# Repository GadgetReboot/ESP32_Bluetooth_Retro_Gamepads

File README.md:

# ESP32_Bluetooth_Retro_Gamepads
Use ESP32 to adapt modern bluetooth game controllers to retro console gamepads<BR><BR>
These PCBs are designed to plug into an ESP32 dev board but can work with 5V power and SPI signals<BR>
https://github.com/GadgetReboot/ESP32_5V_Dev_Board  <BR><BR>
The sketch is set up to auto detect which PCB is plugged in and send out the appropriate gamepad controls
based on PS4 controller activity.<br><br>
Video:<br><br>

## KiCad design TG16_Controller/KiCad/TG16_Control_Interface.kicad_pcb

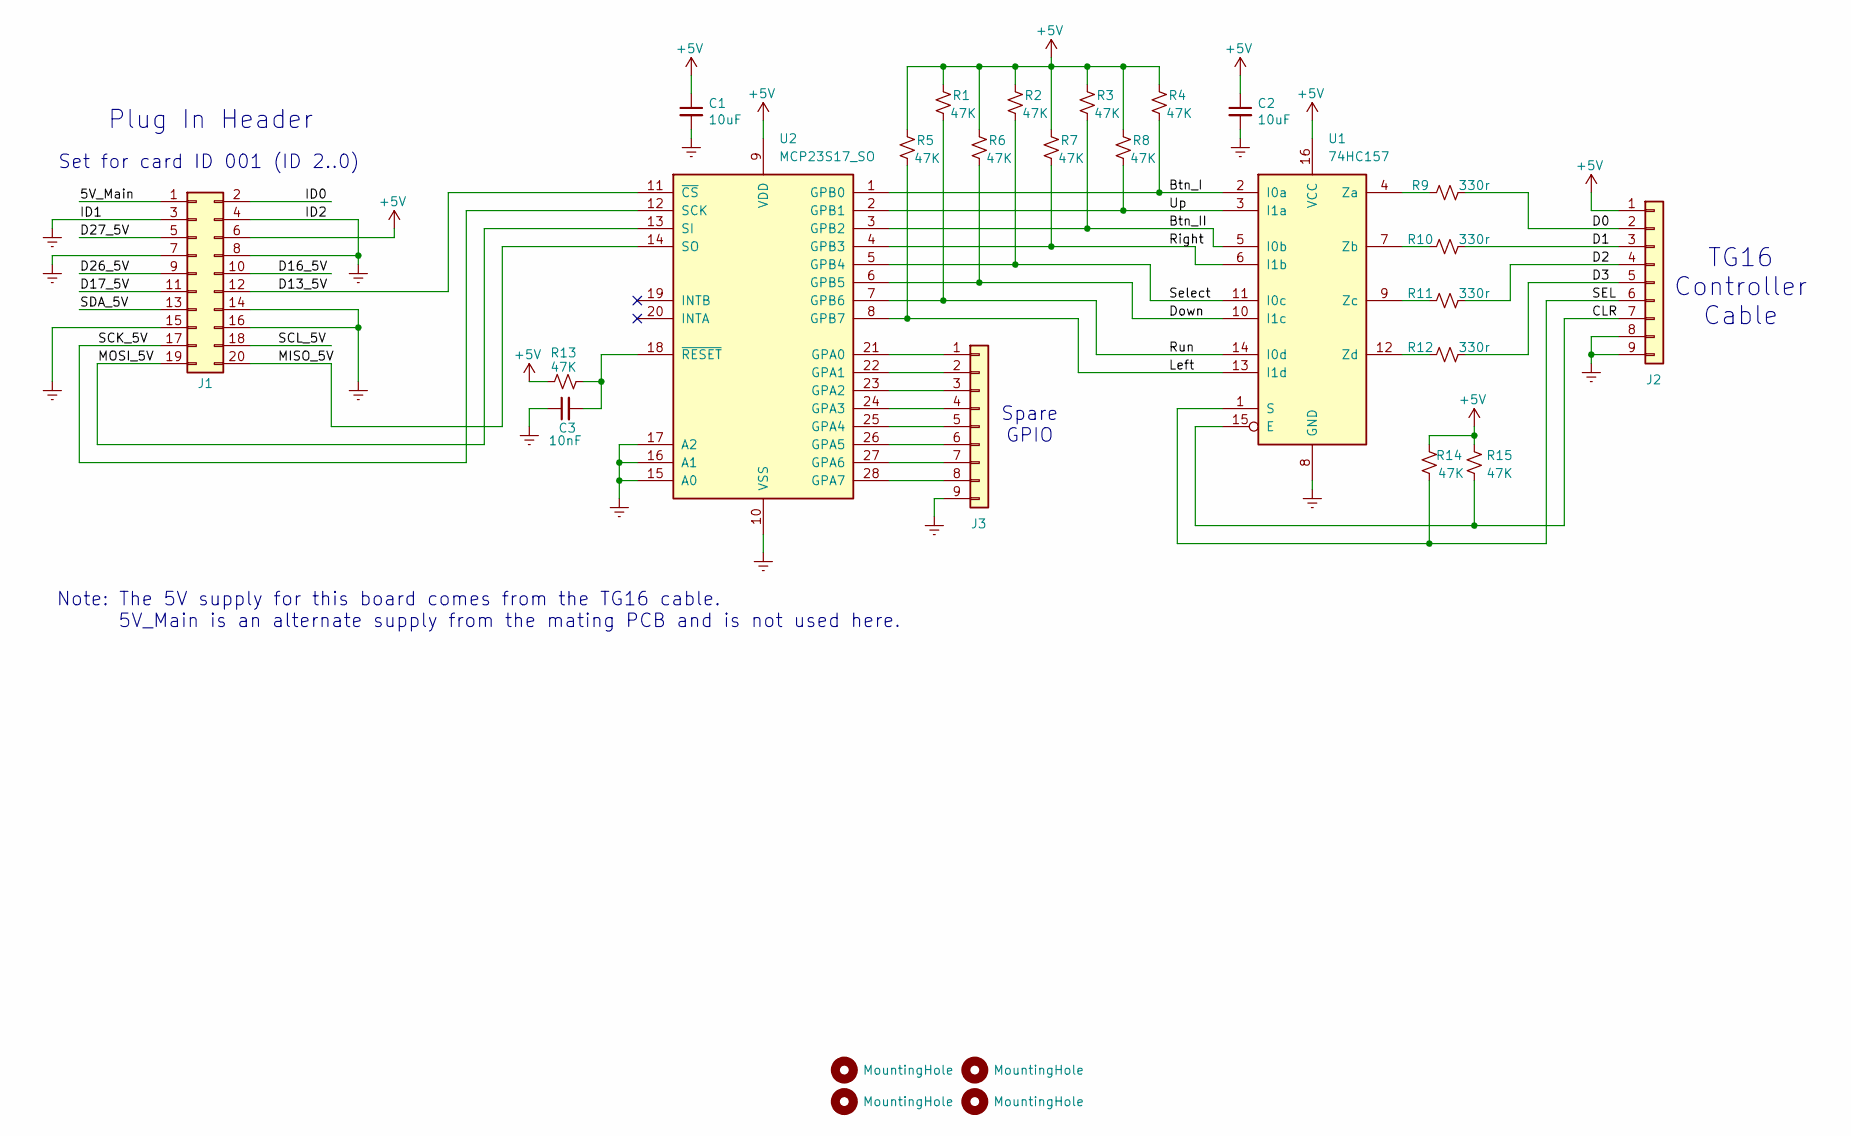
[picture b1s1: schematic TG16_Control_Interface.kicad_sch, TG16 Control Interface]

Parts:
C1, C2: 10uF; C_0805_2012Metric_Pad1.18x1.45mm_HandSolder
C3: 10nF; C_0805_2012Metric_Pad1.18x1.45mm_HandSolder
H1, H2, H3, H4: MountingHole; MountingHole_3.5mm
J1: Conn_02x10_Odd_Even; PinHeader_2x10_P2.54mm_Horizontal
J2: Conn_01x09; JST_XH_S9B-XH-A_1x09_P2.50mm_Horizontal
J3: Conn_01x09; PinHeader_1x09_P2.54mm_Vertical
R1, R2, R3, R4, R5, R6, R7, R8, R13, R14, R15: 47K; R_0805_2012Metric_Pad1.20x1.40mm_HandSolder
R9, R10, R11, R12: 330r; R_0805_2012Metric_Pad1.20x1.40mm_HandSolder
U1: 74HC157; SO-16_3.9x9.9mm_P1.27mm
U2: MCP23S17_SO; SOIC-28W_7.5x17.9mm_P1.27mm

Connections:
+5V: C1.1, C2.1, J1.6, J2.1, R1.1, R2.1, R3.1, R4.1, R5.1, R6.1, R7.1, R8.1, R13.1, R14.1, R15.1, U1.16 (VCC), U2.9 (VDD)
/5V_Main: J1.1
/Btn_I: R4.2, U1.2 (I0a), U2.1 (GPB0)
/Btn_II: R3.2, U1.5 (I0b), U2.3 (GPB2)
/CLR: J2.7, R15.2, U1.15 (E)
/D0: J2.2, R9.2
/D1: J2.3, R10.2
/D2: J2.4, R11.2
/D3: J2.5, R12.2
/D13_5V: J1.12, U2.11 (~CS)
/D16_5V: J1.10
/D17_5V: J1.11
/D26_5V: J1.9
/D27_5V: J1.5
/Down: R6.2, U1.10 (I1c), U2.6 (GPB5)
/ID0: J1.2
/Left: R5.2, U1.13 (I1d), U2.8 (GPB7)
/MISO_5V: J1.20, U2.14 (SO)
/MOSI_5V: J1.19, U2.13 (SI)
/Right: R7.2, U1.6 (I1b), U2.4 (GPB3)
/Run: R1.2, U1.14 (I0d), U2.7 (GPB6)
/SCK_5V: J1.17, U2.12 (SCK)
/SCL_5V: J1.18
/SDA_5V: J1.13
/SEL: J2.6, R14.2, U1.1 (S)
/Select: R2.2, U1.11 (I0c), U2.5 (GPB4)
/Up: R8.2, U1.3 (I1a), U2.2 (GPB1)
GNDREF: C1.2, C2.2, C3.1, J1.3, J1.4, J1.7, J1.8, J1.14, J1.15, J1.16, J2.8, J2.9, J3.9, U1.8 (GND), U2.10 (VSS), U2.15 (A0), U2.16 (A1), U2.17 (A2)
unnamed: J3.1, U2.21 (GPA0)
unnamed: J3.2, U2.22 (GPA1)
unnamed: J3.3, U2.23 (GPA2)
unnamed: J3.4, U2.24 (GPA3)
unnamed: J3.5, U2.25 (GPA4)
unnamed: J3.6, U2.26 (GPA5)
unnamed: J3.7, U2.27 (GPA6)
unnamed: J3.8, U2.28 (GPA7)
unnamed: R9.1, U1.4 (Za)
unnamed: R10.1, U1.7 (Zb)
unnamed: R11.1, U1.9 (Zc)
unnamed: R12.1, U1.12 (Zd)
unnamed: C3.2, R13.2, U2.18 (~RESET)

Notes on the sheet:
Spare GPIO
TG16 Controller Cable
Set for card ID 001 (ID 2..0)
Plug In Header
Note: The 5V supply for this board comes from the TG16 cable. 5V_Main is an alternate supply from the mating PCB and is not used here.

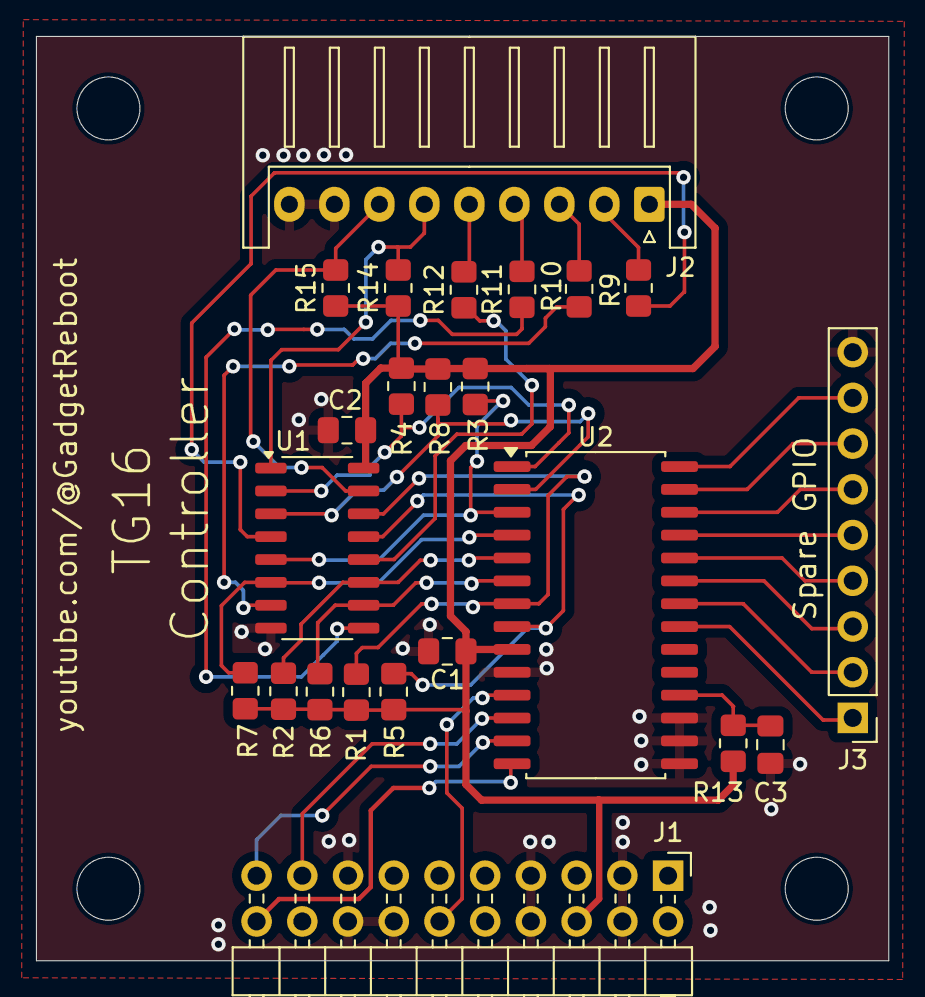
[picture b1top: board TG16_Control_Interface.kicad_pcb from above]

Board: 2 copper layers, 47.3 x 51.4 mm, 27 parts (0 on the bottom side), 33 nets.

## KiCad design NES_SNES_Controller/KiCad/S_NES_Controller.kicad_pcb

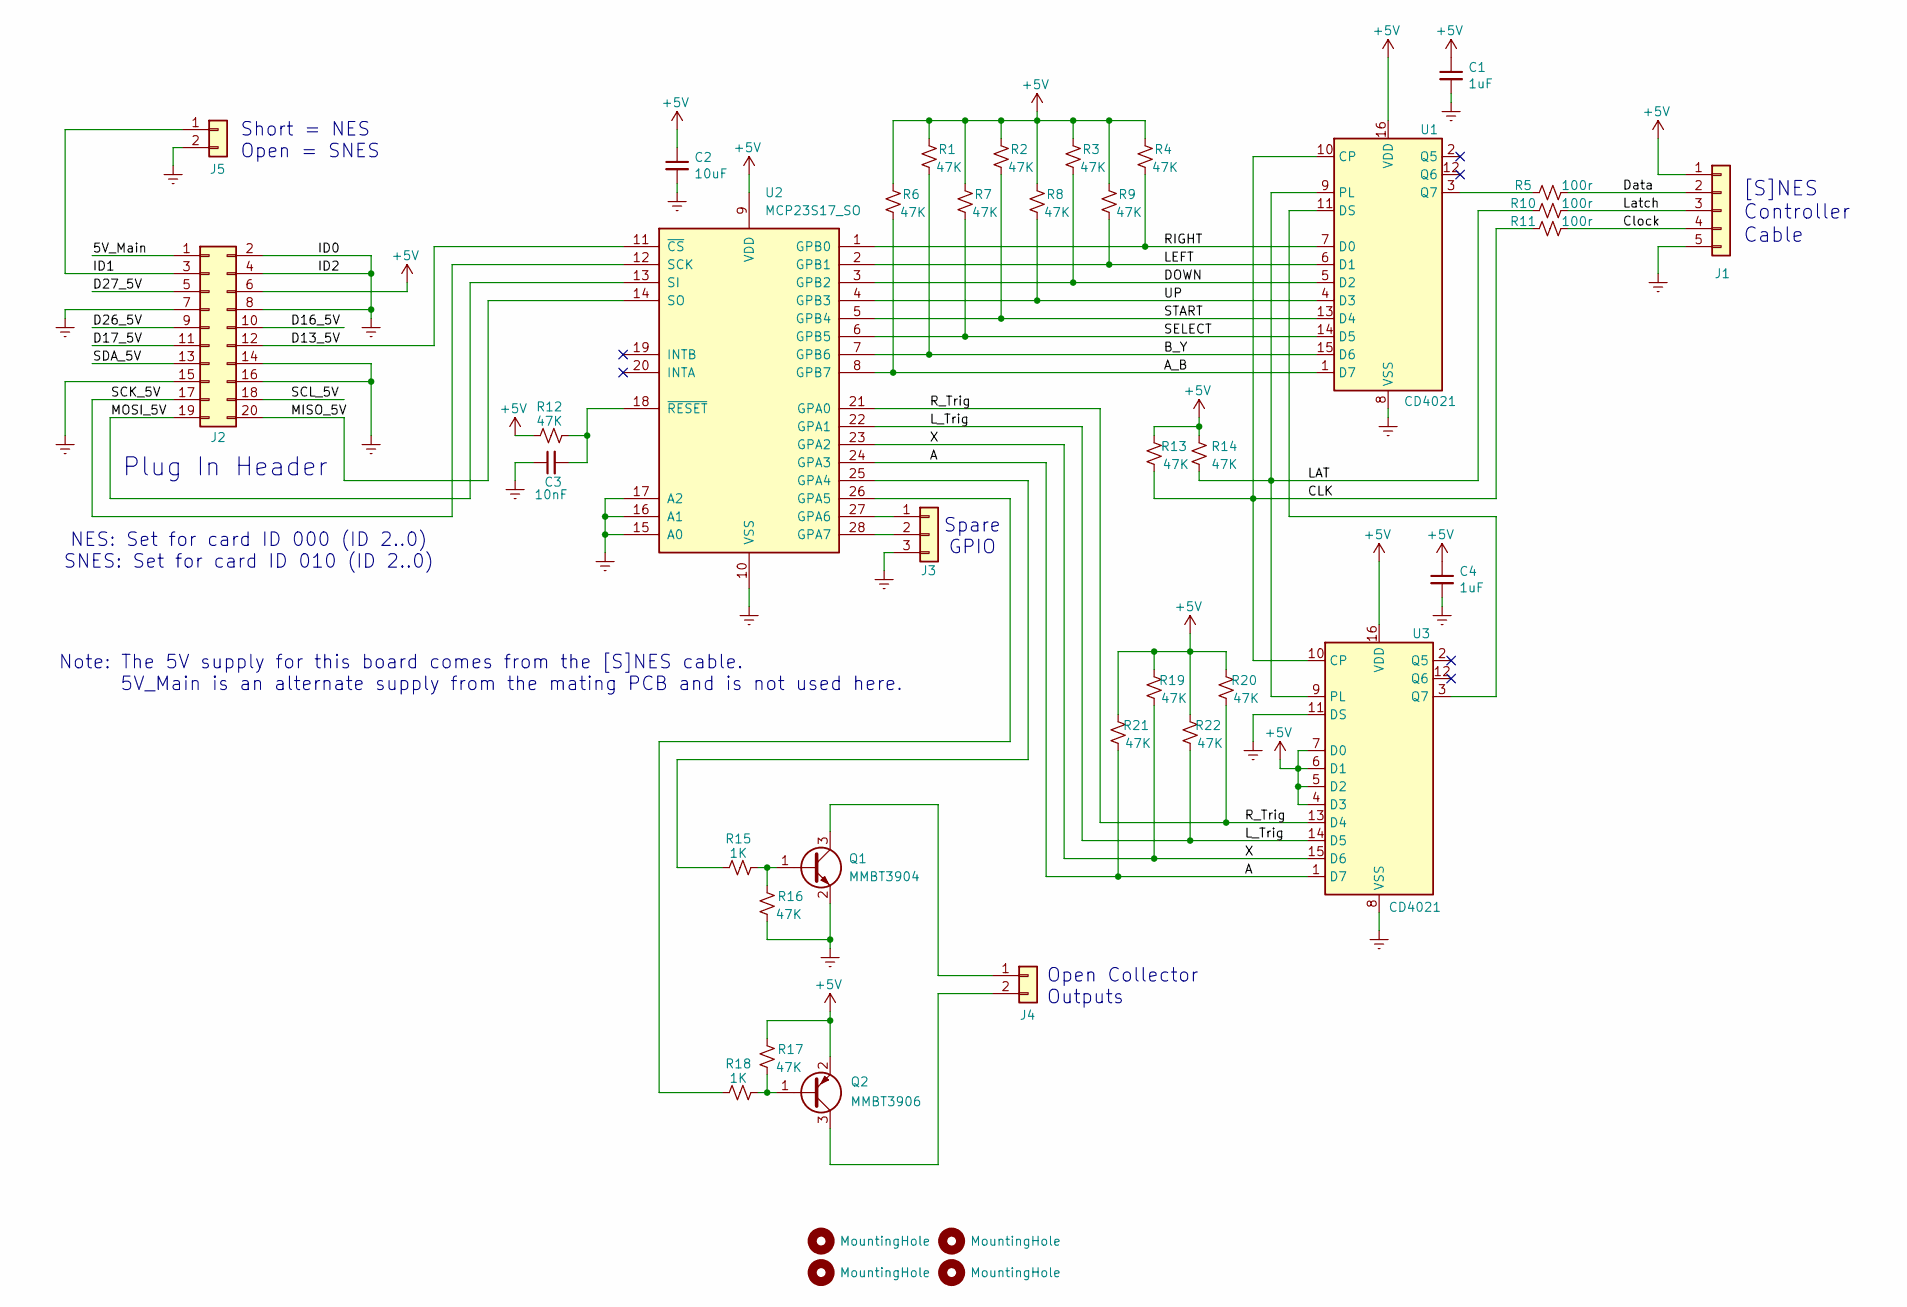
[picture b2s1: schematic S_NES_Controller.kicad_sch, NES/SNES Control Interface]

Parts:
C1, C4: 1uF; C_0805_2012Metric_Pad1.18x1.45mm_HandSolder
C2: 10uF; C_0805_2012Metric_Pad1.18x1.45mm_HandSolder
C3: 10nF; C_0805_2012Metric_Pad1.18x1.45mm_HandSolder
H1, H2, H3, H4: MountingHole; MountingHole_3.5mm
J1: Conn_01x05; JST_XH_S5B-XH-A_1x05_P2.50mm_Horizontal
J2: Conn_02x10_Odd_Even; PinHeader_2x10_P2.54mm_Horizontal
J3: Conn_01x03; PinHeader_1x03_P2.54mm_Vertical
J4, J5: Conn_01x02; PinHeader_1x02_P2.54mm_Vertical
Q1: MMBT3904; SOT-23
Q2: MMBT3906; SOT-23
R1, R2, R3, R4, R6, R7, R8, R9, R12, R13, R14, R16, R17, R19, R20, R21, R22: 47K; R_0805_2012Metric_Pad1.20x1.40mm_HandSolder
R5, R10, R11: 100r; R_0805_2012Metric_Pad1.20x1.40mm_HandSolder
R15, R18: 1K; R_0805_2012Metric_Pad1.20x1.40mm_HandSolder
U1, U3: CD4021; SOIC-16_3.9x9.9mm_P1.27mm; Voltage 5V; mouser# 595-CD4021BM96
U2: MCP23S17_SO; SOIC-28W_7.5x17.9mm_P1.27mm

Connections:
+5V: C1.1, C2.1, C4.1, J1.1, J2.6, Q2.2 (E), R1.1, R2.1, R3.1, R4.1, R6.1, R7.1, R8.1, R9.1, R12.1, R13.1, R14.1, R17.1, R19.1, R20.1, R21.1, R22.1, U1.16 (VDD), U2.9 (VDD), U3.4 (D3), U3.5 (D2), U3.6 (D1), U3.7 (D0), U3.16 (VDD)
/5V_Main: J2.1
/A: R21.2, U2.24 (GPA3), U3.1 (D7)
/A_B: R6.2, U1.1 (D7), U2.8 (GPB7)
/B_Y: R1.2, U1.15 (D6), U2.7 (GPB6)
/CLK: R11.1, R13.2, U1.10 (CP), U3.10 (CP)
/Clock: J1.4, R11.2
/D13_5V: J2.12, U2.11 (~CS)
/D16_5V: J2.10
/D17_5V: J2.11
/D26_5V: J2.9
/D27_5V: J2.5
/DOWN: R3.2, U1.5 (D2), U2.3 (GPB2)
/Data: J1.2, R5.2
/ID1: J2.3, J5.1
/LAT: R10.1, R14.2, U1.9 (PL), U3.9 (PL)
/LEFT: R9.2, U1.6 (D1), U2.2 (GPB1)
/L_Trig: R22.2, U2.22 (GPA1), U3.14 (D5)
/Latch: J1.3, R10.2
/MISO_5V: J2.20, U2.14 (SO)
/MOSI_5V: J2.19, U2.13 (SI)
/RIGHT: R4.2, U1.7 (D0), U2.1 (GPB0)
/R_Trig: R20.2, U2.21 (GPA0), U3.13 (D4)
/SCK_5V: J2.17, U2.12 (SCK)
/SCL_5V: J2.18
/SDA_5V: J2.13
/SELECT: R7.2, U1.14 (D5), U2.6 (GPB5)
/START: R2.2, U1.13 (D4), U2.5 (GPB4)
/UP: R8.2, U1.4 (D3), U2.4 (GPB3)
/X: R19.2, U2.23 (GPA2), U3.15 (D6)
GNDREF: C1.2, C2.2, C3.1, C4.2, J1.5, J2.2, J2.4, J2.7, J2.8, J2.14, J2.15, J2.16, J3.3, J5.2, Q1.2 (E), R16.2, U1.8 (VSS), U2.10 (VSS), U2.15 (A0), U2.16 (A1), U2.17 (A2), U3.8 (VSS), U3.11 (DS)
unnamed: J3.1, U2.27 (GPA6)
unnamed: J3.2, U2.28 (GPA7)
unnamed: J4.1, Q1.3 (C)
unnamed: J4.2, Q2.3 (C)
unnamed: Q1.1 (B), R15.2, R16.1
unnamed: Q2.1 (B), R17.2, R18.2
unnamed: U1.11 (DS), U3.3 (Q7)
unnamed: R5.1, U1.3 (Q7)
unnamed: R15.1, U2.25 (GPA4)
unnamed: R18.1, U2.26 (GPA5)
unnamed: C3.2, R12.2, U2.18 (~RESET)

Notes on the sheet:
Spare GPIO
Open Collector Outputs
[S]NES Controller Cable
NES: Set for card ID 000 (ID 2..0) SNES: Set for card ID 010 (ID 2..0)
Short = NES Open = SNES
Plug In Header
Note: The 5V supply for this board comes from the [S]NES cable. 5V_Main is an alternate supply from the mating PCB and is not used here.

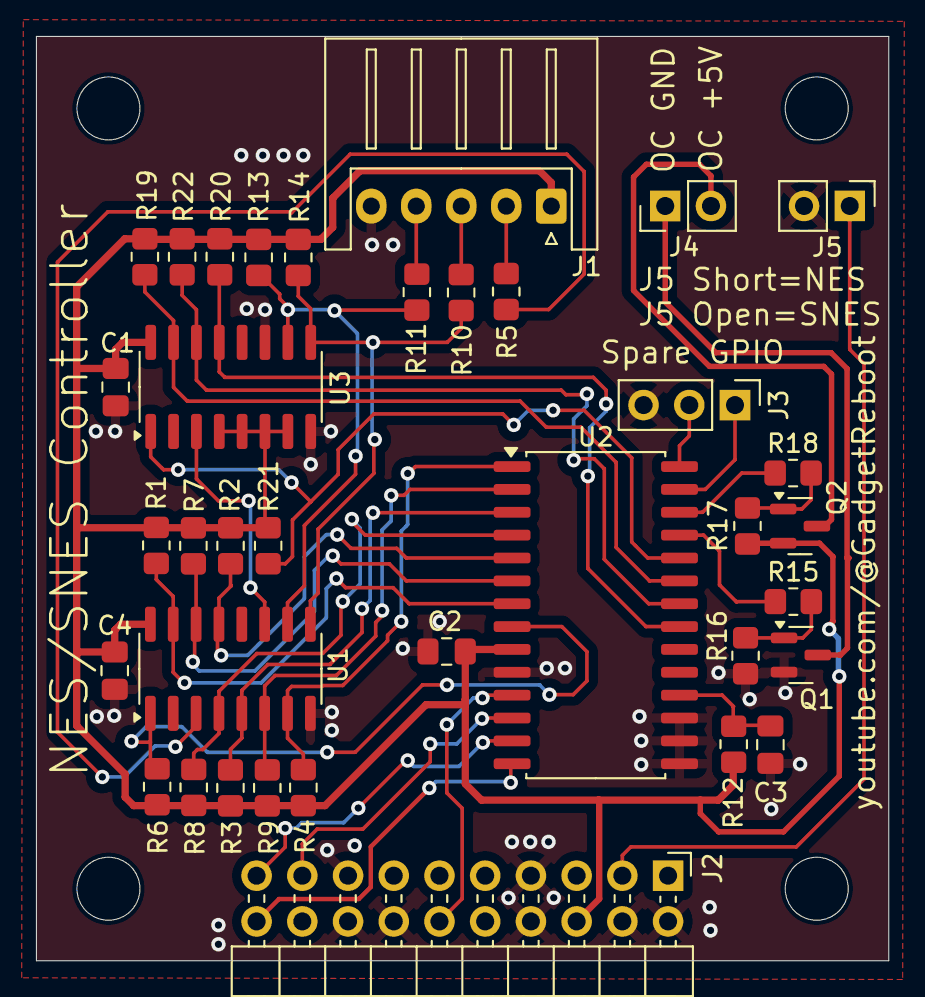
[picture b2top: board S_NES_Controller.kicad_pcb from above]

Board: 2 copper layers, 47.3 x 51.4 mm, 40 parts (0 on the bottom side), 35 nets.
